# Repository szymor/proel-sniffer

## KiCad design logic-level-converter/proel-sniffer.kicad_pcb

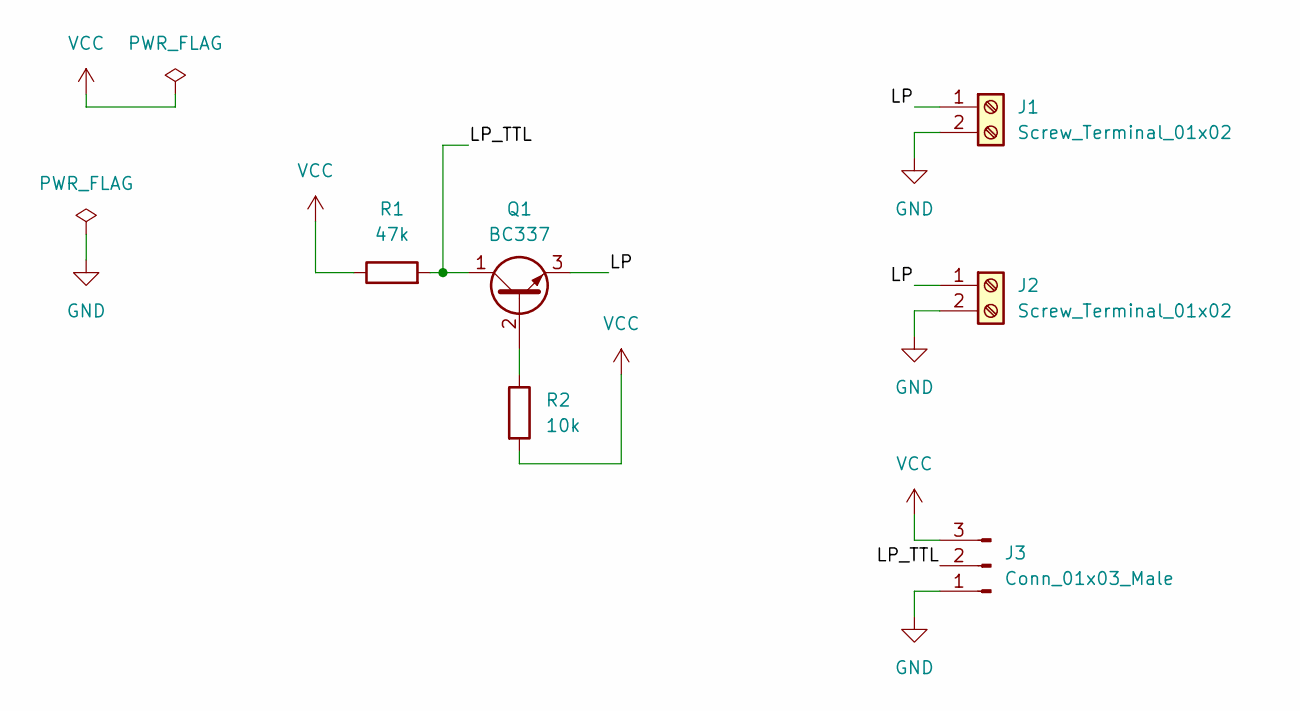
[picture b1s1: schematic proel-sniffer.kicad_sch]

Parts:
J1, J2: Screw_Terminal_01x02; TerminalBlock_Altech_AK300-2_P5.00mm
J3: Conn_01x03_Male; PinHeader_1x03_P2.54mm_Vertical
Q1: BC337; TO-92
R1: 47k; R_Axial_DIN0207_L6.3mm_D2.5mm_P7.62mm_Horizontal
R2: 10k; R_Axial_DIN0207_L6.3mm_D2.5mm_P7.62mm_Horizontal

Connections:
/LP: J1.1, J2.1, Q1.3 (E)
/LP_TTL: J3.2, Q1.1 (C), R1.2
GND: J1.2, J2.2, J3.1
unnamed: Q1.2 (B), R2.1
VCC: J3.3, R1.1, R2.2

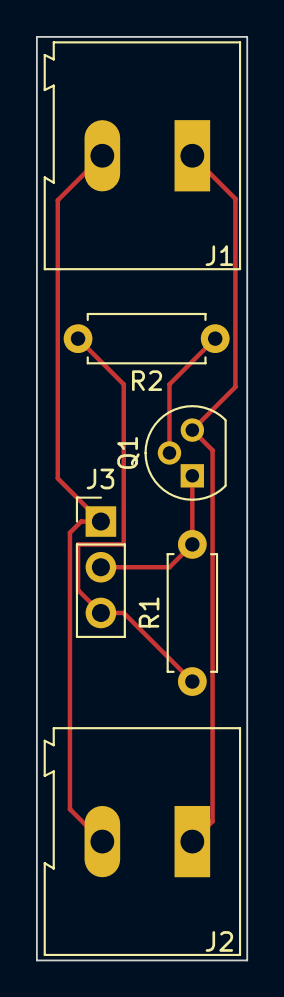
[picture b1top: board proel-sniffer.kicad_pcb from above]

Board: 2 copper layers, 11.7 x 51.3 mm, 6 parts (0 on the bottom side), 5 nets.

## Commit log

2024-10-23 initial
2024-10-29 reorganize files, add saleae captures
2024-10-29 add hw design files for wifi sniffer
2024-10-29 add nodemcu binary
2024-10-29 add init script
2024-10-29 add proel protocol analyzer with unit tests
2024-10-30 remove redundant function naming
2024-10-30 change schematics
2024-10-30 modify L+ to LVTTL converter
2024-10-31 add gpio interrupt trigger, add mqtt lwt
2024-10-31 add unit tests in C
2024-10-31 add avr boilerplate code
2024-10-31 add new test cases
2024-10-31 add new test case to unit tests, add some avr code
2024-11-01 first working proof of concept
2024-11-03 major hw redesign
2024-11-03 add protection diode for adc
2024-11-03 polish lua script
2024-11-06 reorganize captures, add mso5354 captures, add descriptions
2024-11-08 add script for converting analog to digital CSVs
2024-11-08 add new unit tests
2024-11-08 reorganize unit test data
2024-11-08 add script for merging test data, add new test cases
2024-11-09 change baud rate, convert line endings
2024-11-09 fix capture description
2024-11-09 add new test case, expand fsm, harden avr firmware
2024-11-10 add filtering capacitor, change crystal to fit UART requirements
2024-11-10 fix typos, set mqtt qos level to 2, add heartbeat
2024-11-11 design enclosure
2024-11-11 redesign enclosure
2024-11-12 adjust screwholes, introduce size tolerance for lid
2024-11-14 add ferrite beads, power down control pin, current probe jumper, replace mcu
2024-11-15 update capacitors, replace jumpers with pin header
2024-11-15 adjust usb hole position, add two ark holes on the lid
2024-11-15 fix ark lid holes
2024-11-15 add debug properties to fsm
2024-11-23 add image preview for captures
2024-12-04 port to ATmega328PB
2024-12-14 add adc and idle voltage measurement, fix fsm debug, fix atmega328pb port, fix debug mqtt messages
2024-12-15 add power management, read flat number from jumpers, remove heartbeat from esp
2024-12-15 fix debug mqtt
2024-12-17 switch terminals in an ARK connector
2024-12-17 fix ark hole dimensions, put screws to front
